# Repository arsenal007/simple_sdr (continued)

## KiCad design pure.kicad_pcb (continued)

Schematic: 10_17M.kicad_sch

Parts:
C23, C24: 270; C_1206_0603; JLCPCB C694496
C25: 120; C_1206_0603; JLCPCB C599667
C26: 22..47nF; C_1206_0603
C32: 100nF; C_1206_0603
D2, D3: BAP50-03; D_SOD-323_HandSoldering; JLCPCB C130411
L5, L6: 0,22uH; Resistor_SMD+THTuniversal_0603to2512_RM10_HandSoldering
L7: 0,47uH; Resistor_SMD+THTuniversal_0603to2512_RM10_HandSoldering
Q6: MMBT2222A; SOT-23
R28: 10k; R_0603_1608Metric_Pad0.98x0.95mm_HandSolder; JLCPCB C25804
R29: 2..4.7k; R_1206_0603

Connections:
12v_BPF: R28.1; also elsewhere on the board
BPF_10_17M: R29.2; also elsewhere on the board
BPF_IN: D3.2 (A); also elsewhere on the board
BPF_OUT: D2.2 (A); also elsewhere on the board
GND: C23.2, C24.2, C26.2, C32.2, Q6.2 (E); also elsewhere on the board
unnamed: C25.2, L7.1
unnamed: C24.1, D2.1 (K), L6.1, L7.2
unnamed: C23.1, C25.1, D3.1 (K), L5.1
unnamed: C26.1, Q6.1 (B), R29.1
unnamed: C32.1, L5.2, L6.2, Q6.3 (C), R28.2

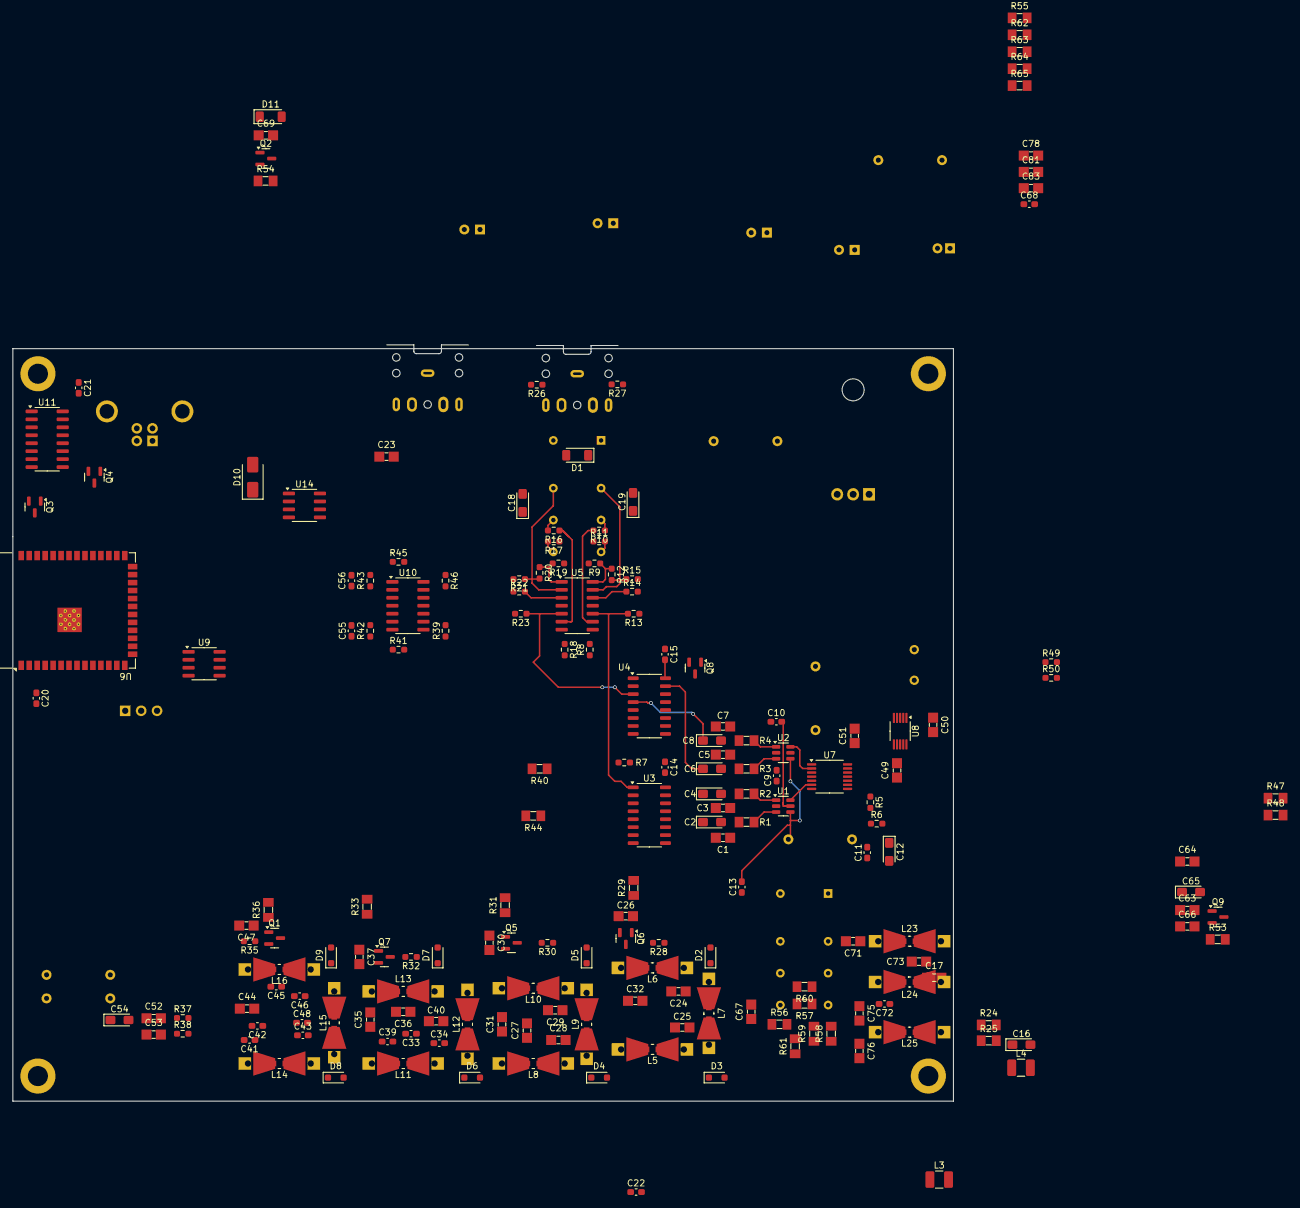
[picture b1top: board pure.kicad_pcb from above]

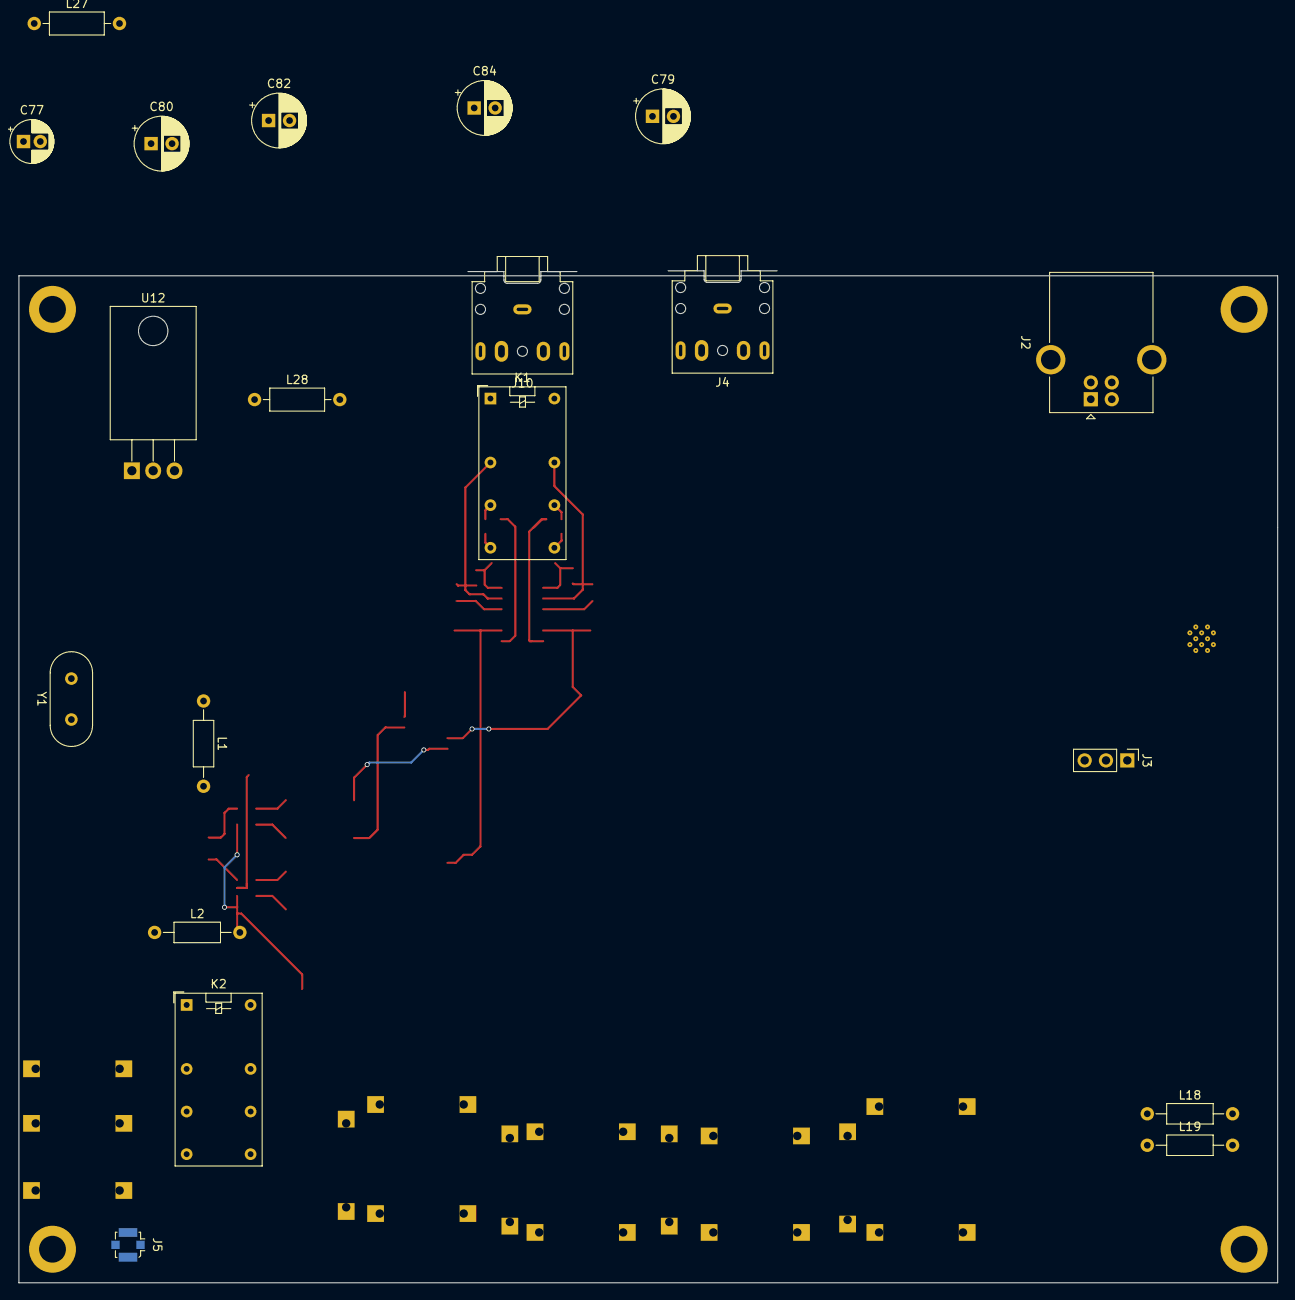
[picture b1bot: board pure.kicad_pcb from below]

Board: 2 copper layers, 150.0 x 120.6 mm, 205 parts (24 on the bottom side), 125 nets.

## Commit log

2023-05-21 progress on schema
2024-04-18 migrate to kicad ver.8
2024-04-18 modify mixer.kicad_sch
2024-04-19 schematics mixer progress, 74HC4053, IF RX. PCB update
2024-04-20 schematics mixer, 74HC4053. IF RX needs JLCPCB numbers. PCB update
2024-04-20 some minor changes, IF RX, 74HC4053, page numbers
2024-04-20 finich IF_RX_Schematics, begin MCU, delete *.sch files
2024-04-21 schematics mixer progress, mcu
2024-04-22 add BPF, add Firmware
2024-04-23 10_17M BPF done
2024-04-25 add custom footprints, progress on schema and PCB
2024-04-29 progress in PCB, schematics some footprints are still missing
2024-05-02 progress on PCB
2024-05-02 progress on schematics and pcb
